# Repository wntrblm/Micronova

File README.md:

# Winterbloom Micronova

Micronova is a small Eurorack power supply.

More details available at https://winterbloom.com/shop/micronova

## Repository layout

This repository contains the hardware design files and user guide for Micronova:

- **hardware/** contains the hardware design files for the board. These are all created using KiCAD.
- **user_guide/** contains the user's guide source files. These are written in Markdown and published using MkDocs.

## License and contributing

Micronova is open-source hardware and software, however, licensing a project like this is a little complicated. Please take a chance to review the [LICENSE](LICENSE.md) file.

We welcome contributions! Please read our [Code of Conduct](CODE_OF_CONDUCT.md) first.

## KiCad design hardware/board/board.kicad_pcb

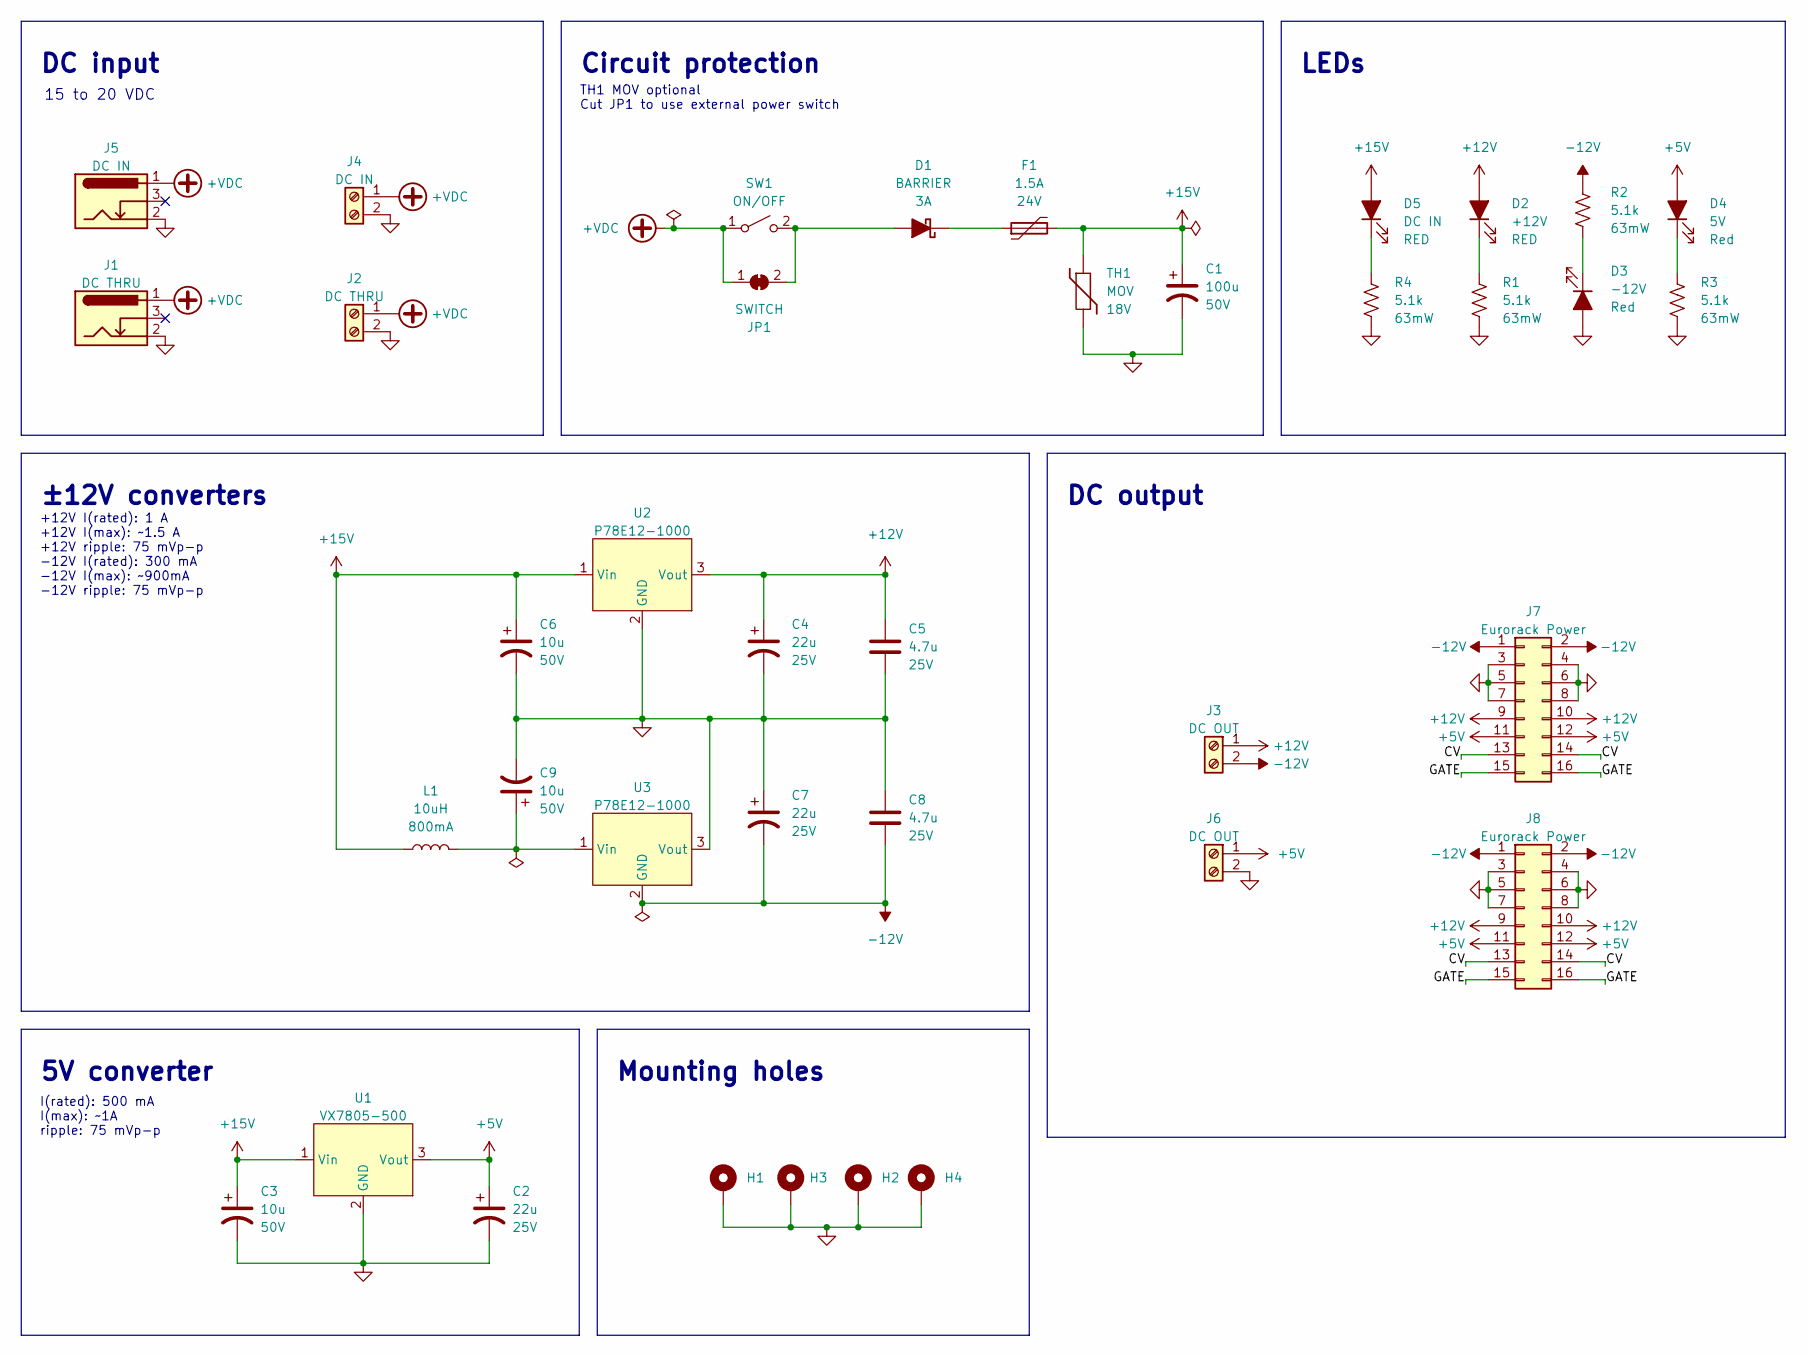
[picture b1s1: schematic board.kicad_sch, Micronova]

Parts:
C1: 100u; CP_Elec_8x10.5; Rating 50V; mpn 865060653010
C2, C4: 22u; C_0805_HandSolder; Rating 25V
C3, C6, C9: 10u; C_1206_HandSolder; Rating 50V
C5, C8: 4.7u; C_0805_HandSolder; Rating 25V
C7: 22u; C_0805_HandSolder
D1: BARRIER; D_SOD-128; Rating 3A; mpn PMEG3030EP,115
D2: +12V; LED_0805_Kingbright_APT2012; mpn APT2012EC
D3: -12V; LED_0805_Kingbright_APT2012; mpn APT2012EC
D4: 5V; LED_0805_Kingbright_APT2012; mpn APT2012EC
D5: DC IN; LED_0805_Kingbright_APT2012; mpn APT2012EC
F1: 1.5A; R_1812_4532Metric_Pad1.30x3.40mm_HandSolder; Rating 24V; mpn 0ZCG0150BF2C
H1, H2, H3, H4: GND; MountingHole_3mm_Pad
J1: DC THRU; BarrelJack_CUI_PJ-102AH_Horizontal; mpn PJ202-A
J2: DC THRU; TerminalBlock_4UCON_1x02_P3.50mm_Horizontal
J3, J6: DC OUT; TerminalBlock_4UCON_1x02_P3.50mm_Horizontal; mpn 20020327-C021B01LF
J4: DC IN; TerminalBlock_4UCON_1x02_P3.50mm_Horizontal
J5: DC IN; BarrelJack_CUI_PJ-102AH_Horizontal; mpn PJ-102A
J7, J8: Eurorack Power; Eurorack_Power_2x8_Shrouded_Lock; mpn 61201621621
JP1: SWITCH; SolderJumper-2_P1.3mm_Bridged2Bar_RoundedPad1.0x1.5mm
L1: 10uH; L_1210_3225Metric_Pad1.42x2.65mm_HandSolder; Rating 800mA; mpn CBC3225T100KR
R1, R2, R3, R4: 5.1k; R_0603_HandSolder; Rating 63mW; mpn AC0603FR-075K1L
SW1: ON/OFF; TerminalBlock_4UCON_1x02_P3.50mm_Horizontal; mpn 2MS1T1B1M2QES
TH1: MOV; R_0805_HandSolder; Rating 18V; mpn MLVC08V018C360
U1: VX7805-500; Converter_DCDC_CUI_VX78-500_THT; mpn VX7805-500
U2, U3: P78E12-1000; Converter_DCDC_CUI_P78E-1000_THT; mpn P78E12-1000

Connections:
+5V: C2.1, D4.2 (A), J6.1, J7.11, J7.12, J8.11, J8.12, U1.3 (Vout)
+12V: C4.1, C5.1, D2.2 (A), J3.1, J7.9, J7.10, J8.9, J8.10, U2.3 (Vout)
+15V: C1.1, C3.1, C6.1, D5.2 (A), F1.2, L1.1, TH1.1, U1.1 (Vin), U2.1 (Vin)
+VDC: J1.1, J2.1, J4.1, J5.1, JP1.1 (A), SW1.1 (A)
-12V: C7.2, C8.2, J3.2, J7.1, J7.2, J8.1, J8.2, R2.1, U3.2 (GND)
/CV: J7.13, J7.14, J8.13, J8.14
/GATE: J7.15, J7.16, J8.15, J8.16
GND: C1.2, C2.2, C3.2, C4.2, C5.2, C6.2, C7.1, C8.1, C9.2, D3.2 (A), H1.1, H2.1, H3.1, H4.1, J1.2, J2.2, J4.2, J5.2, J6.2, J7.3, J7.4, J7.5, J7.6, J7.7, J7.8, J8.3, J8.4, J8.5, J8.6, J8.7, J8.8, R1.2, R3.2, R4.2, TH1.2, U1.2 (GND), U2.2 (GND), U3.3 (Vout)
unnamed: C9.1, L1.2, U3.1 (Vin)
unnamed: D1.1 (K), F1.1
unnamed: D1.2 (A), JP1.2 (B), SW1.2 (B)
unnamed: D2.1 (K), R1.1
unnamed: D3.1 (K), R2.2
unnamed: D4.1 (K), R3.1
unnamed: D5.1 (K), R4.1

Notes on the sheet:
DC output
I(rated): 500 mA I(max): ~1A ripple: 75 mVp-p
5V converter
±12V converters
TH1 MOV optional Cut JP1 to use external power switch
15 to 20 VDC
DC input
Mounting holes
+12V I(rated): 1 A +12V I(max): ~1.5 A +12V ripple: 75 mVp-p -12V I(rated): 300 mA -12V I(max): ~900mA -12V ripple: 75 mVp-p
LEDs
Circuit protection

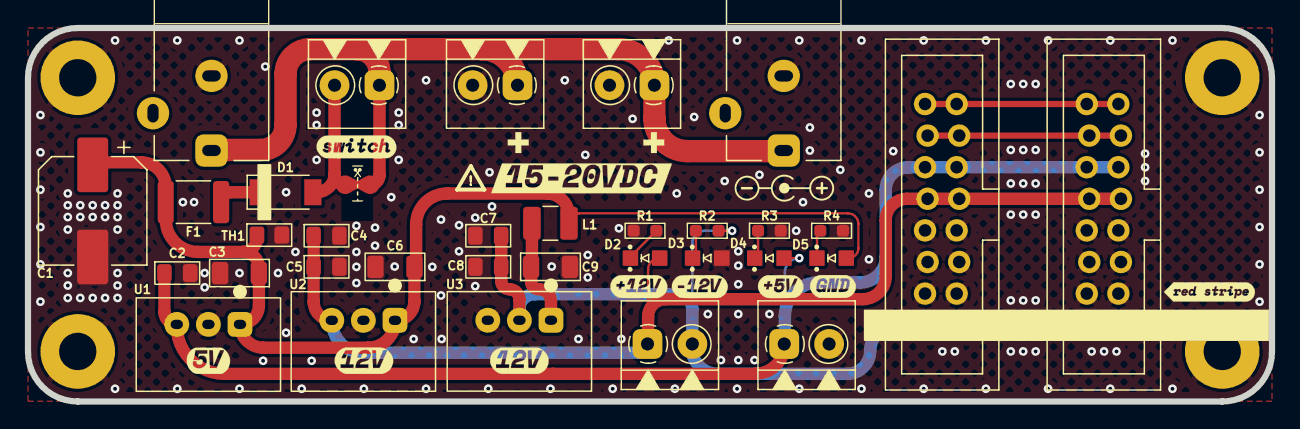
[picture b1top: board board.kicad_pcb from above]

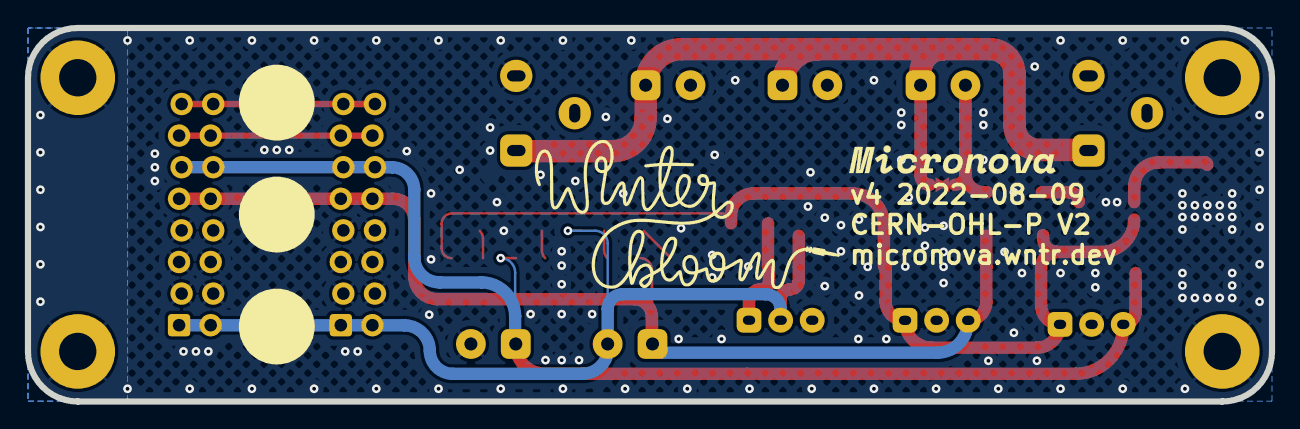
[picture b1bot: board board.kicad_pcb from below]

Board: 2 copper layers, 100.0 x 30.0 mm, 41 parts (2 on the bottom side), 15 nets.

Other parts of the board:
OSHW: OSHW-Logo_5.7x6mm_Copper
POLARITY: Symbol_Barrel_Polarity
WNTR: LOGO

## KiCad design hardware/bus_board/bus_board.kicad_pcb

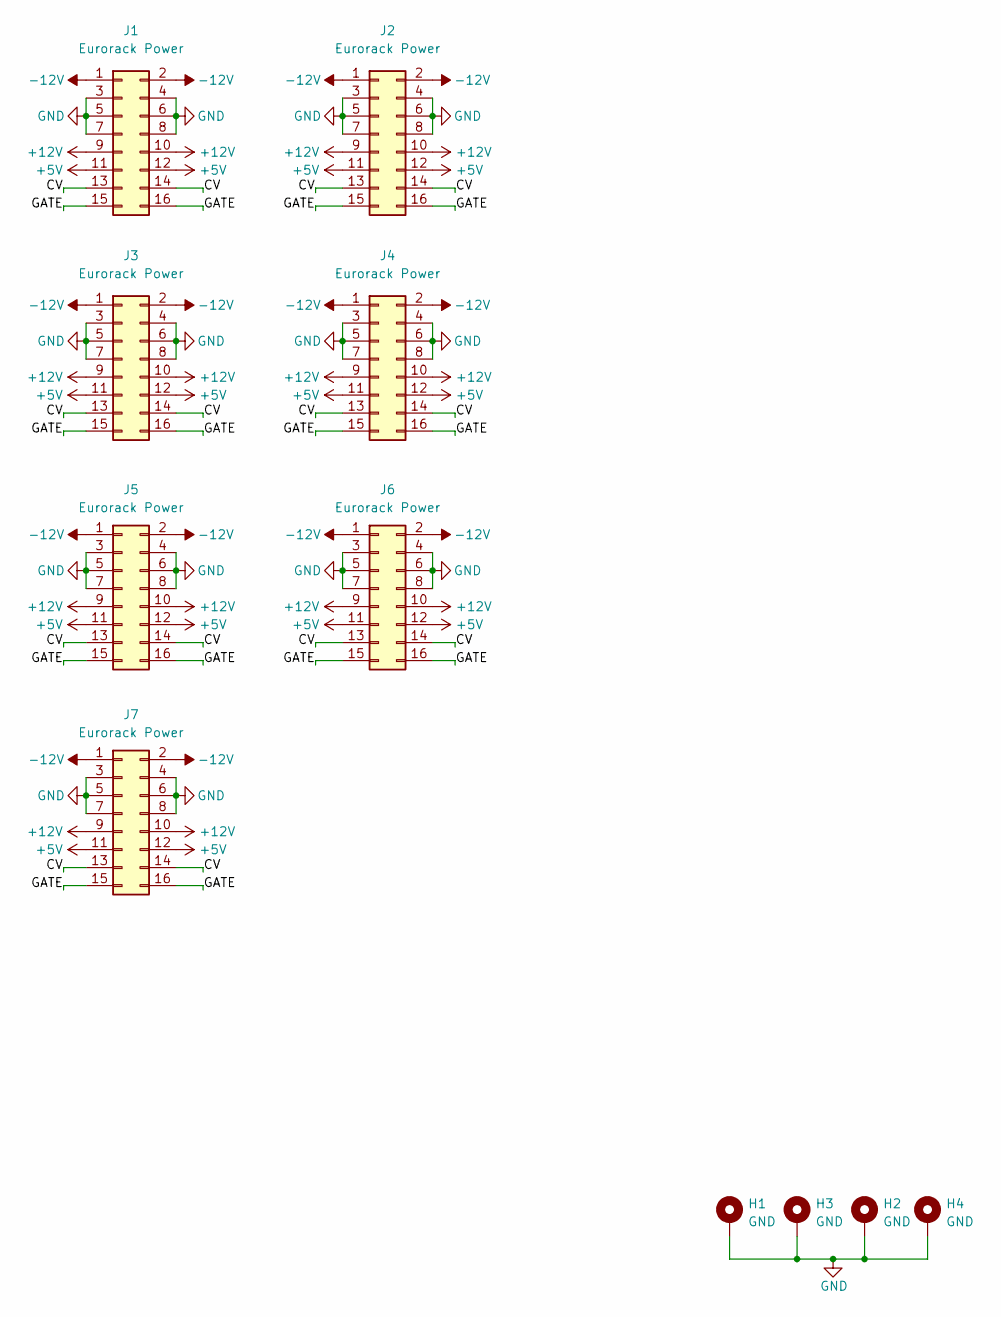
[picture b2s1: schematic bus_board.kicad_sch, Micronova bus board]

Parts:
H1, H2, H3, H4: GND; MountingHole_3mm_Pad
J1, J2, J3, J4, J5, J6, J7: Eurorack Power; Eurorack_Power_2x8_Shrouded_Lock; mpn 61201621621

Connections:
+5V: J1.11, J1.12, J2.11, J2.12, J3.11, J3.12, J4.11, J4.12, J5.11, J5.12, J6.11, J6.12, J7.11, J7.12
+12V: J1.9, J1.10, J2.9, J2.10, J3.9, J3.10, J4.9, J4.10, J5.9, J5.10, J6.9, J6.10, J7.9, J7.10
-12V: J1.1, J1.2, J2.1, J2.2, J3.1, J3.2, J4.1, J4.2, J5.1, J5.2, J6.1, J6.2, J7.1, J7.2
/CV: J1.13, J1.14, J2.13, J2.14, J3.13, J3.14, J4.13, J4.14, J5.13, J5.14, J6.13, J6.14, J7.13, J7.14
/GATE: J1.15, J1.16, J2.15, J2.16, J3.15, J3.16, J4.15, J4.16, J5.15, J5.16, J6.15, J6.16, J7.15, J7.16
GND: H1.1, H2.1, H3.1, H4.1, J1.3, J1.4, J1.5, J1.6, J1.7, J1.8, J2.3, J2.4, J2.5, J2.6, J2.7, J2.8, J3.3, J3.4, J3.5, J3.6, J3.7, J3.8, J4.3, J4.4, J4.5, J4.6, J4.7, J4.8, J5.3, J5.4, J5.5, J5.6, J5.7, J5.8, J6.3, J6.4, J6.5, J6.6, J6.7, J6.8, J7.3, J7.4, J7.5, J7.6, J7.7, J7.8

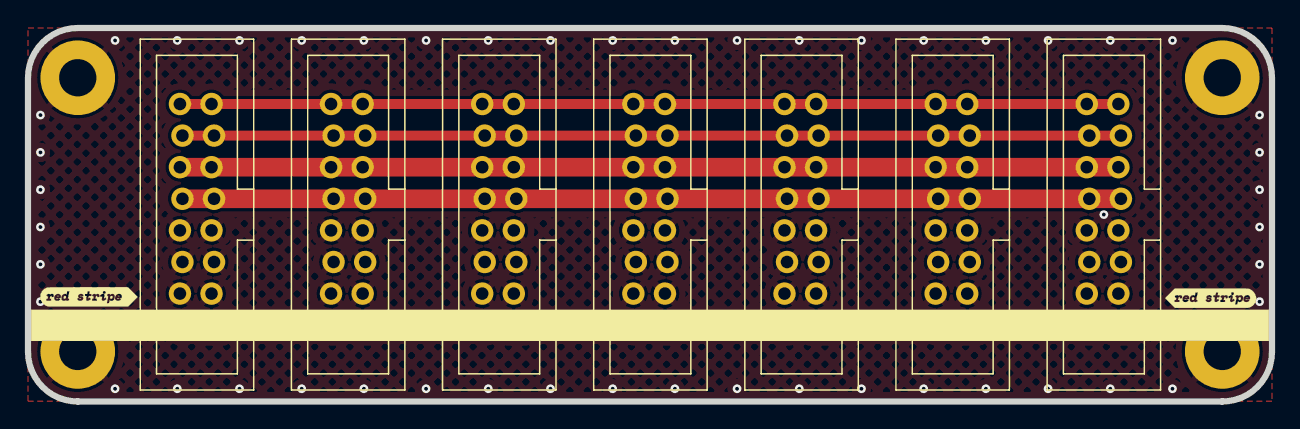
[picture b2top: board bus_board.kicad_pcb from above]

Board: 2 copper layers, 100.0 x 30.0 mm, 12 parts (1 on the bottom side), 6 nets.

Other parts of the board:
OSHW: OSHW-Logo_5.7x6mm_Copper

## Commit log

2022-05-23 Initial repo setup
2022-05-23 Add initial hardware design
2022-05-23 Update page details in schematic
2022-05-23 Use new winterbloom footprints
2022-05-28 Update some MPNs
2022-06-05 Add OSHW and polarity symbols to the PCB
2022-06-05 Resolve ERC errors related to non-schematic footprints
2022-06-14 Use hatched fills
2022-06-14 Add passive bus board
2022-06-20 Move some silkscreen around just a little
2022-07-31 Update schematic with new name and organize it a little
2022-07-31 Update the PCB with the new name
2022-07-31 Update the busboard with new name
2022-07-31 Update readme and license with new name
2022-08-04 Widen some traces
2022-08-04 Widen some traces- again
2022-08-10 hardware: various updates (v4)
    - switched to winterbloom footprints for caps and resistors
    - use fancytext labels
2022-08-10 hardware: use fancytext labels on busboard
2022-08-13 Add some helpful dimensions
2022-08-31 First draft of user guide
2022-08-31 add photos for user guide
2022-08-31 Add some more images, do some revisions
2022-08-31 Add kit contents svg
2022-08-31 Fix a few more TODOs
2022-09-01 Fixup images in dark mode
2022-09-01 Fix link
2022-09-01 Fix product name in license
2022-09-01 Add GitHub Actions for user guide
2022-09-02 Add PDF of schematic
2022-09-03 Fixup some MPNs
2022-09-16 Add open source hardware certification
2022-09-26 user guide: fix small typo
2023-03-29 docs/build: fix typo
2024-04-07 user guide: switch to wintersong theme
2024-05-27 user guide: Add a link to cornicopia project
2024-05-27 Deployed bf79eec with MkDocs version: 1.6.0
2025-01-30 hardware: Added faceplate

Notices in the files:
hardware/board/board.kicad_pcb:
CERN-OHL-P V2
